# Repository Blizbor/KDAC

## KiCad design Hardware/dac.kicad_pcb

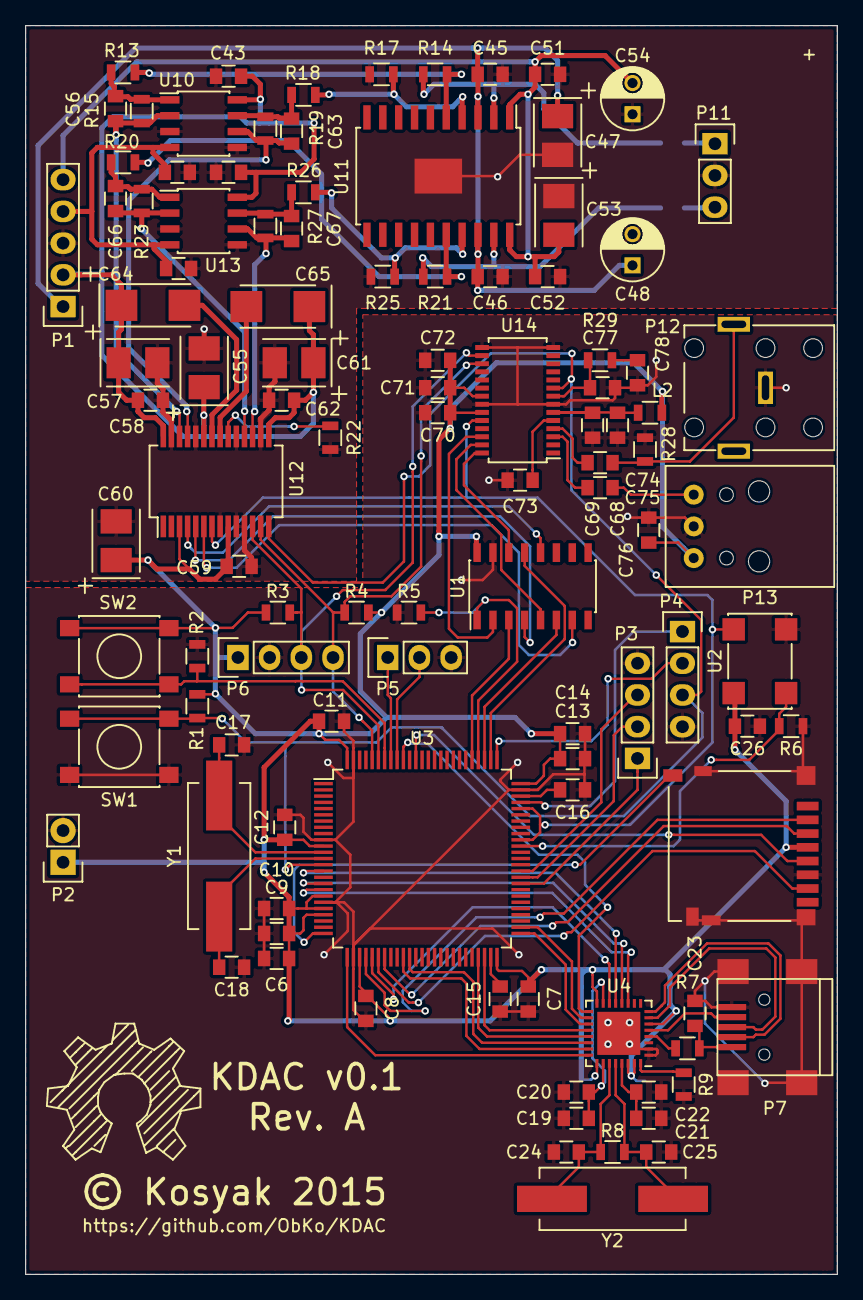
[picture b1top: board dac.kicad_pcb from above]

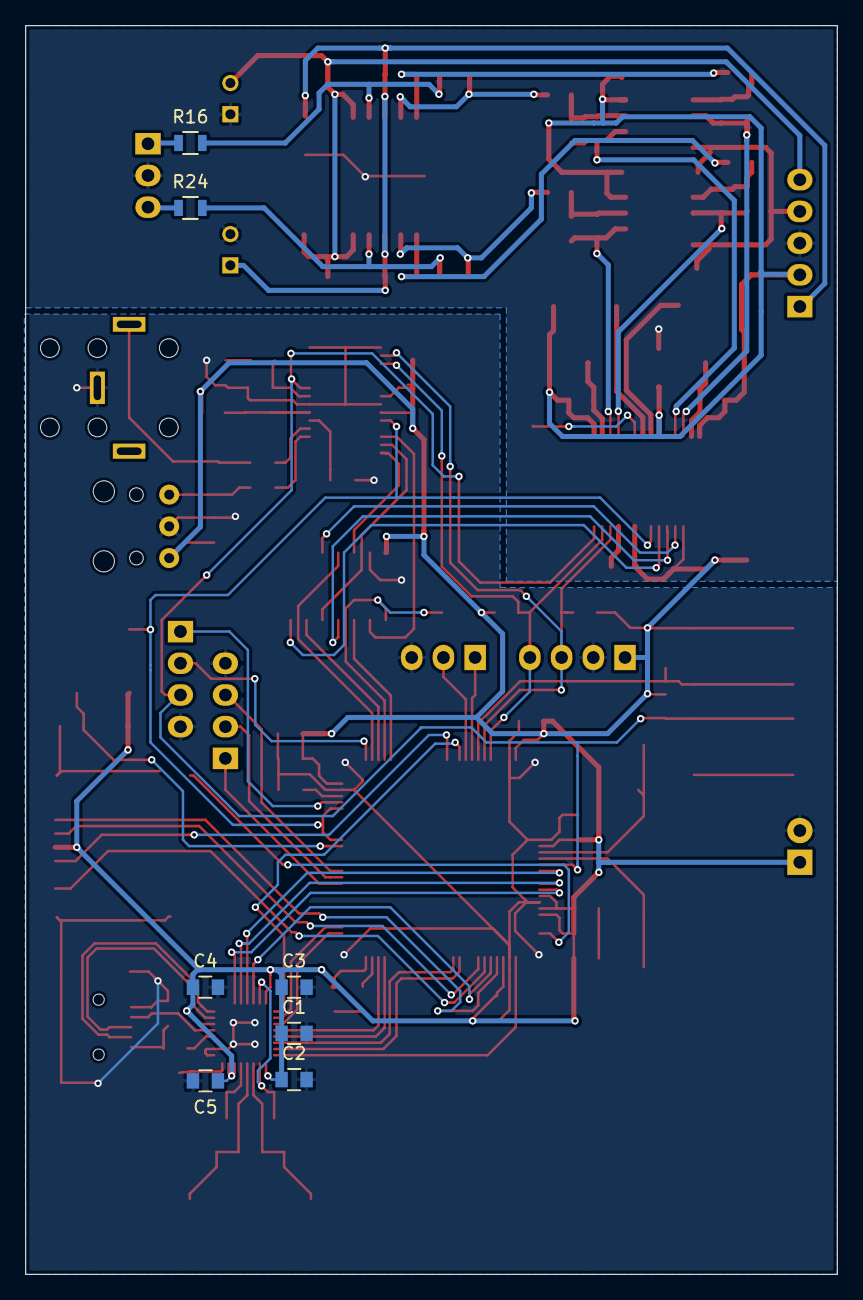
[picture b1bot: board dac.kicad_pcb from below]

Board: 2 copper layers, 65.0 x 100.0 mm, 113 parts (7 on the bottom side), 88 nets.

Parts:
C1, C6, C14, C15, C16, C19, C21, C23, C68, C72: 4.7µF; C_0805
C2, C3, C4, C5, C7, C8, C9, C10, C11, C12, C13, C20, C22, C26, C43, C44, C45, C46, C49, C50, C51, C52, C58, C59, C62, C69, C70, C71, C76: 0.1µF; C_0805
C17, C18, C24, C25: 22pF; C_0805
C47, C53, C55, C57, C60, C61: 10µF; TantalC_SizeB_EIA-3528_Reflow
C48, C54: 100µF; C_Radial_D5_L11_P2.5
C56, C63, C66, C67: 2.7nF; C_0805
C64, C65: 47µF; TantalC_SizeC_EIA-6032_Reflow
C73, C74, C75: 10nF; C_0805
C77: 1nF; C_0805
C78: 22nF; C_0805
CON1: SD_Card; DM3D-SF
L2: BEAD; R_0805
P1: ANALOG_POWER; Pin_Header_Straight_1x05
P2: DIGITAL_POWER; Pin_Header_Straight_1x02
P3: ENCODER; Pin_Header_Straight_1x04
P4: SWDIO; Pin_Header_Straight_1x04
P5: UART; Pin_Header_Straight_1x03
P6: OLED; Pin_Header_Straight_1x04
P7: USB_OTG; USB_Mini-B
P11: JACK; Pin_Header_Straight_1x03
P12: S/PDIF; RCA
P13: TORX147; TORX147PL
R1, R2, R3, R4, R5, R6: 4.7k; R_0805
R7, R13, R14, R15, R17, R18, R19, R20, R21, R23, R25, R26, R27: 1k; R_0805
R8: 1M; R_0805
R9: 12k; R_0805
R16, R24: 39; R_0805
R22: 10k; R_0805
R28: 75; R_0805
R29: 3k; R_0805
SW1: RESET; SW_SPST_PTS645
SW2: BOOT; SW_SPST_PTS645
U1: 74LS157; SOIC-16_3.9x9.9mm_Pitch1.27mm
U2: 49.152MHz; XO
U3: STM32F407VE; LQFP-100_14x14mm_Pitch0.5mm
U4: USB3300; QFN-32-1EP_5x5mm_Pitch0.5mm
U10, U13: OPA2134; SOIC-8_3.9x4.9mm_Pitch1.27mm
U11: TPA6120A2; SOIC-20_7.5x12.8mm_Pitch1.27mm
U12: PCM1792A; SSOP-28_5.3x10.2mm_Pitch0.65mm
U14: CS8416-Z; TSSOP-28_4.4x9.7mm_Pitch0.65mm
Y1, Y2: 12MHz; Crystal_HC49-SD_SMD

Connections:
+3V3: C1.1, C2.1, C3.1, C4.1, C5.1, C6.1, C7.1, C8.1, C9.1, C10.1, C11.1, C12.1, C13.1, C14.1, C26.1, C59.2, C60.1, C70.1, C71.1, C72.1, C76.1, CON1.4, L2.1, P2.1, P6.1, P13.3, R1.1, R3.1, R4.1, SW2.1, U1.16, U2.4, U3.11, U3.19, U3.21, U3.22, U3.28, U3.50, U3.75, U3.100, U4.6, U4.16, U4.25, U4.30, U4.31, U12.3, U12.9, U14.21, U14.23
+5V: C43.2, C44.2, C55.1, C57.1, C58.2, C61.1, C62.2, C64.1, C65.1, P1.2, U10.8, U12.15, U12.23, U12.28, U13.8
+12V: C45.2, C46.2, C47.1, C48.1, P1.1, U11.3, U11.18
-5V: C49.1, C50.1, P1.4, U10.4, U13.4
-12V: C51.1, C52.1, C53.2, C54.2, P1.5, U11.1, U11.20
/DAC/I2S_BCK: U1.7, U12.6
/DAC/I2S_LRCK: U1.12, U12.4
/DAC/I2S_MCK: U2.3, U3.66, U3.71, U12.7, U14.24
/DAC/I2S_SD: U1.4, U12.5
/DAC/~RST: P4.3, R1.2, SW1.2, U3.14, U12.14, U14.9
/MCU/CARD: CON1.10, U3.25
/MCU/D_N: P7.2, U4.8
/MCU/D_P: P7.3, U4.7
/MCU/I2C_SCL: P6.3, R3.2, U3.95, U12.12, U14.16
/MCU/I2C_SDA: P6.4, R4.2, U3.96, U12.13, U14.17
/MCU/I2S_BCK: U1.6, U3.78
/MCU/I2S_LRCK: U1.13, U3.77
/MCU/I2S_SD: U1.3, U3.80
/MCU/I2S_SEL: R5.1, U1.1, U3.79
/MCU/SPI_CS: CON1.1, U3.29
/MCU/SPI_MISO: CON1.7, U3.31
/MCU/SPI_MOSI: CON1.2, U3.32
/MCU/SPI_SCK: CON1.5, U3.89
/MCU/ULPI_CLK: U3.30, U4.14
/MCU/ULPI_D0: U3.26, U4.24
/MCU/ULPI_D1: U3.35, U4.23
/MCU/ULPI_D2: U3.36, U4.22
/MCU/ULPI_D3: U3.47, U4.21
/MCU/ULPI_D4: U3.48, U4.20
/MCU/ULPI_D5: U3.51, U4.19
/MCU/ULPI_D6: U3.52, U4.18
/MCU/ULPI_D7: U3.91, U4.17
/MCU/ULPI_DIR: U3.17, U4.12
/MCU/ULPI_NXT: U3.18, U4.11
/MCU/ULPI_STP: U3.15, U4.13
/MCU/XO_EN: R6.1, U2.1, U3.65
/SPDIF Receiver/I2S_BCK: U1.5, U14.27
/SPDIF Receiver/I2S_LRCK: U1.14, U14.28
/SPDIF Receiver/I2S_SD: U1.2, U14.26
GNDA: C43.1, C44.1, C45.1, C46.1, C47.2, C48.2, C49.2, C50.2, C51.2, C52.2, C53.1, C54.1, C55.2, C57.2, C58.1, C59.1, C60.2, C61.2, C62.1, P1.3, P11.2, R17.1, R22.1, R25.1, U10.3, U10.5, U12.8, U12.10, U12.11, U12.16, U12.19, U12.24, U12.27, U13.3, U13.5
GNDD: C1.2, C2.2, C3.2, C4.2, C5.2, C6.2, C7.2, C8.2, C9.2, C10.2, C11.2, C12.2, C13.2, C14.2, C15.1, C16.1, C17.2, C18.2, C19.1, C20.1, C21.1, C22.1, C23.2, C24.2, C25.2, C26.2, C68.2, C69.2, C70.2, C71.2, C72.2, C73.2, C76.2, C77.2, C78.2, CON1.6, CON1.12, P2.2, P3.4, P4.4, P5.3, P6.2, P7.5, P7.6, P12.1, P13.2, R2.2, R5.2, R6.2, R9.2, R28.2, SW1.1, U1.15, U2.2, U3.10, U3.20, U3.27, U3.74, U3.99, U4.1, U4.2, U4.33, U14.7, U14.14, U14.15, U14.22
unnamed: C15.2, U3.49
unnamed: C16.2, U3.73
unnamed: C17.1, U3.12, Y1.1
unnamed: C18.1, U3.13, Y1.2
unnamed: C19.2, C20.2, U4.15, U4.26
unnamed: C21.2, C22.2, U4.29
unnamed: C23.1, P7.1, R7.1
unnamed: C24.1, R8.1, U4.27, Y2.1
unnamed: C25.1, R8.2, U4.28, Y2.2
unnamed: C56.1, R13.2, R15.1, U10.1
unnamed: C56.2, R15.2, U10.2, U12.26
unnamed: C63.1, R18.2, R19.1, U10.7
unnamed: C63.2, R19.2, U10.6, U12.25
unnamed: C64.2, U12.22
unnamed: C65.2, U12.21
unnamed: C66.1, R20.2, R23.1, U13.1
unnamed: C66.2, R23.2, U12.18, U13.2
unnamed: C67.1, R26.2, R27.1, U13.7
unnamed: C67.2, R27.2, U12.17, U13.6
unnamed: C68.1, C69.1, L2.2, U14.6
unnamed: C73.1, U14.5
unnamed: C74.1, U14.4
unnamed: C74.2, P12.2, R28.1
unnamed: C75.1, U14.3
unnamed: C75.2, P13.1
unnamed: C77.1, R29.1, U14.8
unnamed: C78.1, R29.2
unnamed: P3.1, U3.59
unnamed: P3.2, U3.60
unnamed: P3.3, U3.61
unnamed: P4.1, U3.72
unnamed: P4.2, U3.76
unnamed: P5.1, U3.93
unnamed: P5.2, U3.92
unnamed: P7.4, U4.5
unnamed: P11.1, R16.1
unnamed: P11.3, R24.1
unnamed: R2.1, SW2.2, U3.94
unnamed: R7.2, U4.4
unnamed: R9.1, U4.32
unnamed: R13.1, R14.2, U11.5
unnamed: R14.1, R16.2, U11.2
unnamed: R17.2, R18.1, U11.4
unnamed: R20.1, R21.2, U11.16
unnamed: R21.1, R24.2, U11.19
unnamed: R22.2, U12.20
unnamed: R25.2, R26.1, U11.17

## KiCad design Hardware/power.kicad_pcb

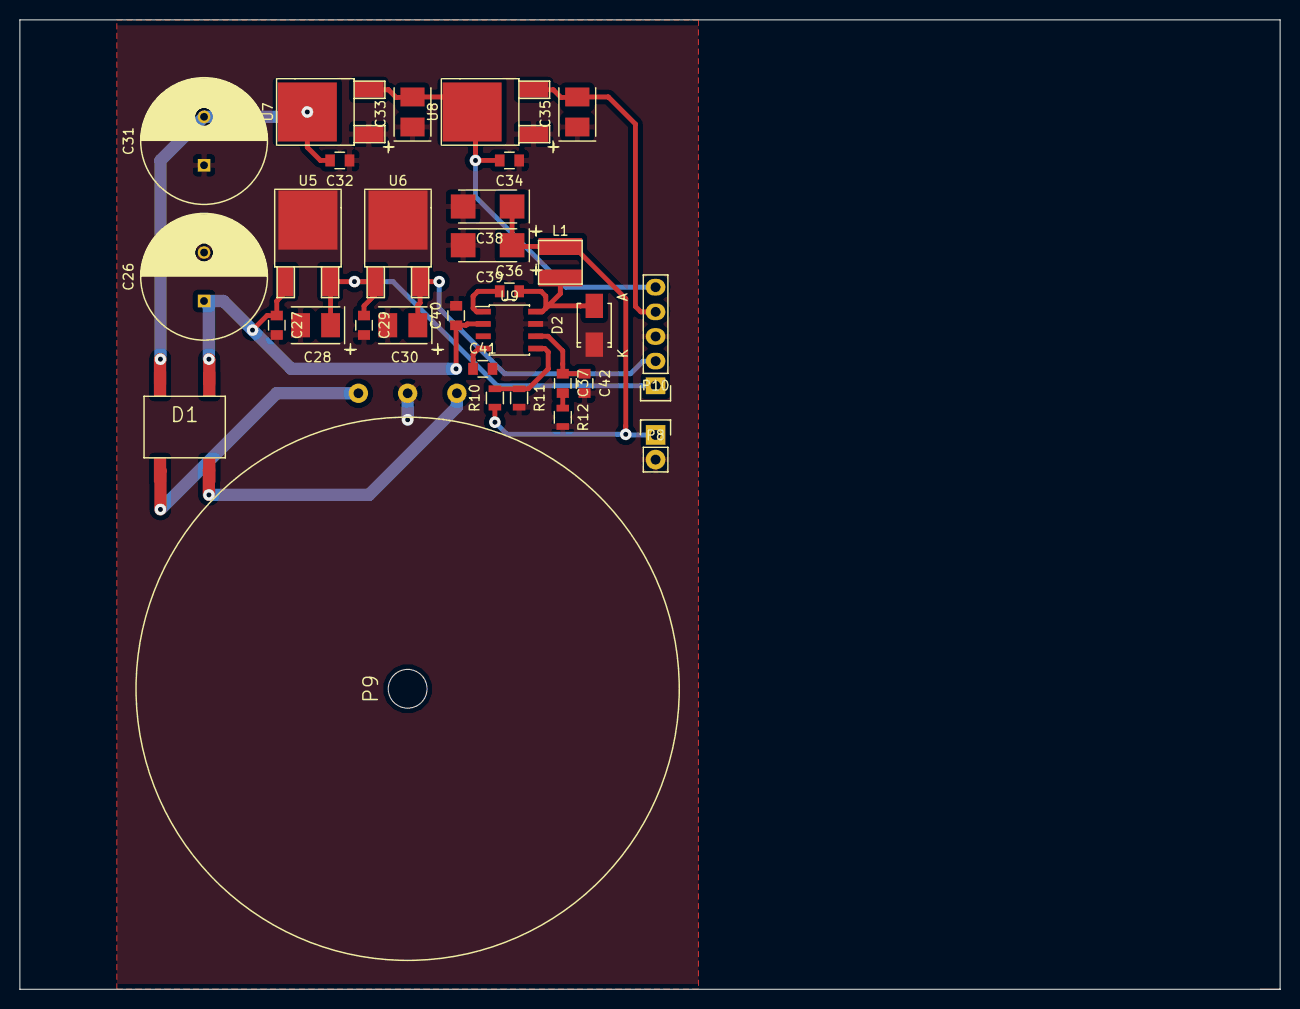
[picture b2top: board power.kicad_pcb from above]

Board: 2 copper layers, 130.0 x 100.0 mm, 31 parts (0 on the bottom side), 16 nets.

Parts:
C26, C31: 1000µF; C_Radial_D13_L21_P5
C27, C29, C32, C34, C36: 0.1µF; C_0805
C28, C30, C33, C35: 10µF; TantalC_SizeB_EIA-3528_Reflow
C37: ~1nF; C_0805
C38, C39: 47µF; TantalC_SizeC_EIA-6032_Reflow
C40: 4.7µF; C_0805
C41: 10nF; C_0805
C42: ~47pF; C_0805
D1: D_Bridge; DB10xS
D2: SS14; Diode-SMA_Standard
L1: 47µH; CD43
P8: ANALOG_POWER; Pin_Header_Straight_1x05
P9: TRANSFORMER; TTP-15
P10: DIGITAL_POWER; Pin_Header_Straight_1x02
R10: 7.5k; R_0805
R11: 2.4k; R_0805
R12: 33k; R_0805
U5: 7812; DPAK-2
U6: 7805; DPAK-2
U7: 7912; DPAK-2
U8: 7905; DPAK-2
U9: TPS54331; SOIC-8_3.9x4.9mm_Pitch1.27mm

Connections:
+3V3: C38.1, C39.1, L1.2, P10.1, R10.1
+5V: C30.1, P8.2, U6.3
+12V: C28.1, C29.1, P8.1, U5.3, U6.1
-5V: C35.2, P8.4, U8.3
-12V: C33.2, C34.2, P8.5, U7.3, U8.2
GNDD: C26.2, C27.2, C28.2, C29.2, C30.2, C31.1, C32.1, C33.1, C34.1, C35.1, C38.2, C39.2, C40.2, C41.2, C42.2, D2.1, P8.3, P9.2, P10.2, R11.2, R12.2, U5.2, U6.2, U7.1, U8.1, U9.7
unnamed: C26.1, C27.1, C40.1, D1.3, U5.1, U9.2
unnamed: C31.2, C32.2, D1.4, U7.2
unnamed: C36.1, U9.1
unnamed: C36.2, D2.2, L1.1, U9.8
unnamed: C37.1, C42.1, U9.6
unnamed: C37.2, R12.1
unnamed: C41.1, U9.4
unnamed: D1.1, P9.1
unnamed: D1.2, P9.3
unnamed: R10.2, R11.1, U9.5

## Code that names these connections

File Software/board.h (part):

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 * PA0  - PIN0                      (input pullup).
 * PA1  - PIN1                      (input pullup).
 * PA2  - CARD_DETECT               (input pullup).
 * PA3  - ULPI_D0                   (alternate 10).
 * PA4  - CARD_CS                   (output pushpull maximum).
 * PA5  - ULPI_CLK                  (alternate 10).
 * PA6  - CARD_MISO                 (alternate 5).
 * PA7  - CARD_MOSI                 (alternate 5).
 * PA8  - PIN8                      (input pullup).
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 * PA12 - MCK_FB                    (alternate 1).
 * PA13 - JTAG_TMS                  (alternate 0).
 * PA14 - JTAG_TCK                  (alternate 0).
 * PA15 - I2S_LRCK                  (alternate 6).
 */
#define VAL_GPIOA_MODER             (PIN_MODE_INPUT(GPIOA_PIN0) |           \
                                     PIN_MODE_INPUT(GPIOA_PIN1) |           \
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/*
 * GPIOB setup:
 *
 * PB0  - ULPI_D1                   (alternate 10).
 * PB1  - ULPI_D2                   (alternate 10).
 * PB2  - PIN2                      (input pullup).
 * PB3  - CARD_SCK                  (alternate 5).
 * PB4  - PIN4                      (input pullup).
 * PB5  - ULPI_D7                   (alternate 10).
 * PB6  - USART1_TX                 (alternate 7).
 * PB7  - USART1_RX                 (alternate 7).
 * PB8  - I2C_SCL                   (alternate 4).
 * PB9  - I2C_SDA                   (alternate 4).
 * PB10 - ULPI_D3                   (alternate 10).
 * PB11 - ULPI_D4                   (alternate 10).
 * PB12 - ULPI_D5                   (alternate 10).
 * PB13 - ULPI_D6                   (alternate 10).
 * PB14 - PIN14                     (input pullup).
 * PB15 - PIN15                     (input pullup).
 */
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/*
 * GPIOC setup:
 *
 * PC0  - ULPI_STP                  (alternate 10).
 * PC1  - PIN1                      (input pullup).
 * PC2  - ULPI_DIR                  (alternate 10).
 * PC3  - ULPI_NXT                  (alternate 10).
 * PC4  - PIN4                      (input pullup).
 * PC5  - PIN5                      (input pullup).
 * PC6  - PIN6                      (input pullup).
 * PC7  - PIN7                      (input pullup).
 * PC8  - MCK_EN                    (output pushpull maximum).
 * PC9  - I2S_MCK                   (alternate 5).
 * PC10 - I2S_BCK                   (alternate 6).
 * PC11 - I2S_SEL                   (output pushpull maximum).
 * PC12 - I2S_SD                    (alternate 6).
 * PC13 - PIN13                     (input pullup).
 * PC14 - PIN14                     (input pullup).
 * PC15 - PIN15                     (input pullup).
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
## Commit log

2015-05-27 Initial commit.
2015-05-27 PCB bugfixes.
2015-05-27 Gerbers & pdf schematic.
2015-09-14 Initial software commit.
    Firmware will be based on ChibiOS/ChibiOS RTOS.
    Nothing useful for now, just config files and application template.
    Project uses ObKo/stm32-cmake as a build system.
2015-09-15 ChibiOS shell using USB CDC through ULPI PHY in FullSpeed mode.
    I2S master clock (MCK) frequency measurement (relative to USB Host SOF).
2015-09-17 Some playing with uGFX and OLED display with SH1106 controller.
2015-09-23 Start work on GUI library.
2015-09-24 More GUI.
2015-09-30 Start working on S/PDIF receiver driver (CS8416).
    Errata for hardware.
2015-10-27 Source selection skeleton.
2015-10-27 Volume control.
2015-10-28 Input selection in GUI.
2015-11-05 USB Audio.
    Based on demo project written for ChibiOS.
    It's a bit buggy and ugly.
    Only FullSpeed for now, so 96 kHz / 16 bit max.

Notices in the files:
Software/board.h:
ChibiOS - Copyright (C) 2006..2015 Giovanni Di Sirio
Licensed under the Apache License, Version 2.0 (the "License");
Hardware/dac.kicad_pcb:
© Kosyak 2015
